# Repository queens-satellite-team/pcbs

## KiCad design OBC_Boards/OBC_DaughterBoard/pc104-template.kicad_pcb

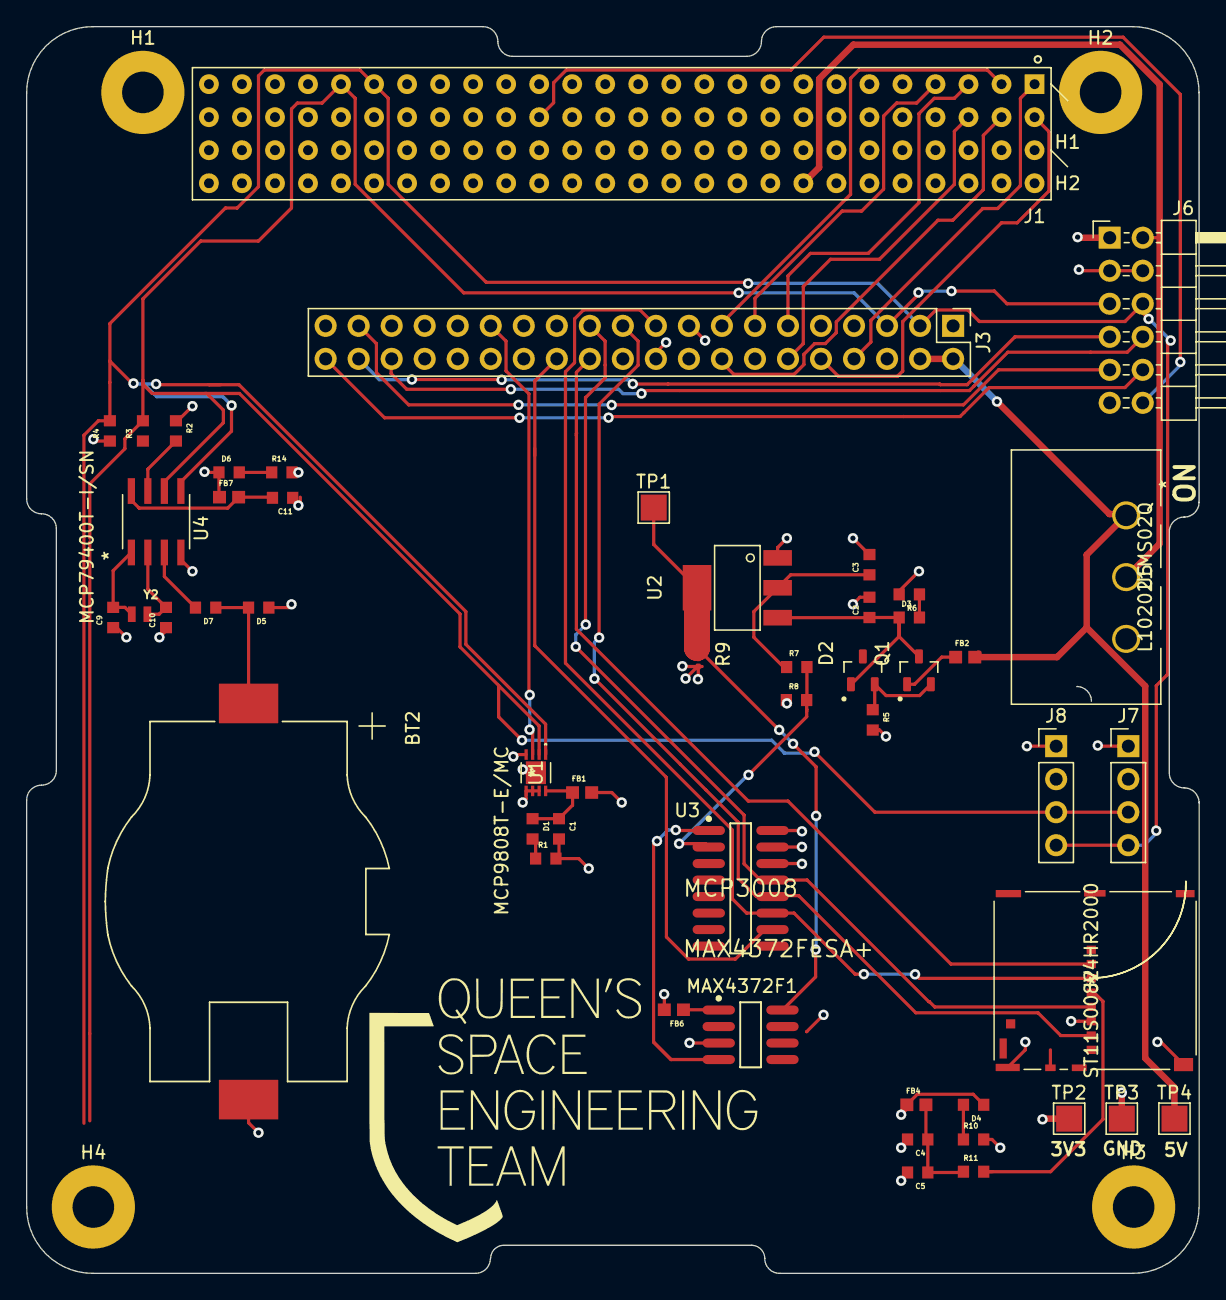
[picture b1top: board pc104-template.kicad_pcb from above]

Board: 4 copper layers, 90.2 x 95.9 mm, 55 parts (0 on the bottom side), 47 nets.

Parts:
BT2: BHSD-2032-SM; BAT_BHSD-2032-SM
C1, C4: 0.1uF; CAPC1608X90N
C2, C5, C11: 10uF; CAPC1608X90N
C3: 22uF; CAPC1608X90N
C9, C10: 18pF; CAPC1608X90N
D1, D3, D4, D6: RED; CAPC1608X90N
D2: D_Zener; SOT91P240X110-3N
D5, D7: DIODE; CAPC1608X90N
FB1, FB2, FB4, FB6, FB7: 100R @ 100 MHz; BEADC1608X75N
H1, H2, H3, H4: MountingHole_Pad; MountingHole_3.2mm_M3_Pad
J1: PC104_Connector; pc104-connector
J2: ST11S008V4HR2000
J3: Raspberry Pi 4 Connector; PinHeader_2x20_P2.54mm_Vertical
J6: Test Connector; PinHeader_2x06_P2.54mm_Horizontal
J7: Temp Sens1 Connector; PinHeader_1x04_P2.54mm_Vertical
J8: Temp Sens2 Connector; PinHeader_1x04_P2.54mm_Vertical
MAX4372F1: MAX4372FESA+; Maxim-MAX4372FESA+-Level_A
Q1: Q_PMOS_DGS; SOT91P240X110-3N
R1, R6, R10, R14: 2.2k; RESC1608X55N
R2, R3, R4, R5, R8: 10k; RESC1608X55N
R7: 20k; RESC1608X55N
R9: 100m; R_0201_0603Metric
R11: 33; RESC1608X55N
TP1, TP3: TestPoint; TestPoint_Pad_2.0x2.0mm
TP2: 3V3; TestPoint_Pad_2.0x2.0mm
TP4: 5V; TestPoint_Pad_2.0x2.0mm
U1: MCP9808T-E/MC; MCP9808T-E&slash_MC
U2: BU33SA5WGWZ-E2-qsat-symb; BU33SA5WGWZ-E2
U3: MCP3008; Microchip-MCP3008-I_SL-Level_A
U4: MCP79400T-I/SN; MCP79400T-I&slash_SN
U5: L102021MS02Q
Y2: CM9V-T1A; XTAL_CM9V-T1A-32.768KHZ-9PF-20PPM-TA-QC

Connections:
3V3_Input: J7.1, J8.1
5VUSB_CHG: J1.32 (H1-32), J6.12
+3.3V: D6.1 (A), FB7.1, R2.1, R3.1, R4.1
+3V3: D4.1 (A), D5.1 (A), FB1.2, FB4.1, FB6.2, J3.1, J3.17, MAX4372F1.6 (RS-), R9.2, TP2.1, U3.15 (Vref), U3.16 (Vdd)
+5V: FB2.2, J3.2, J3.4, TP4.1, U5.1
/Current Monitor/CH1: R7.2, R8.2, U3.2 (CH1)
/Current Monitor/PM_Input: MAX4372F1.8 (RS+), R9.1, TP1.1, U2.4 (Vout)
ADCS_INT: J1.5 (H1-5), J3.11
BAT_INT: J1.7 (H1-7), J3.13
COMM_CTS: J1.3 (H1-3), J3.15
COMM_RTS: J1.4 (H1-4), J3.16
COMM_RXD: J1.2 (H1-2), J3.10
COMM_TXD: J1.1 (H1-1), J3.8
EPS_INT: J1.6 (H1-6), J3.12
GND: BT2.-, C1.2, C2.1, C3.2, C4.2, C5.2, C9.1, C10.1, C11.1, H1.1, H2.1, H3.1, H4.1, J1.61 (H2-9), J1.66 (H1-14), J1.69 (H2-17), J1.73 (H2-21), J1.74 (H1-22), J1.81 (H2-29), J1.82 (H1-30), J1.84 (H1-32), J1.99 (H2-47), J1.100 (H2-48), J2.6 (VSS), J2.11 (GND1), J2.12 (GND2), J2.13 (GND3), J2.14 (GND4), J2.15 (GND5), J2.16 (GND6), J2.17 (GND7), J3.6, J3.9, J3.14, J3.20, J3.25, J3.30, J3.34, J3.39, J6.3, J6.4, J7.2, J8.2, MAX4372F1.3 (GND), R1.2, R5.2, R6.2, R8.1, R10.2, R14.2, TP3.1, U1.4 (GND), U1.5 (A2), U1.6 (A1), U1.7 (A0), U1.9 (EPAD), U2.1 (GND), U3.14 (AGND), U4.4 (VSS)
GPIO5: J3.29, U1.3 (ALERT)
GPIO16: J3.36, J6.8
GPIO20: J3.38, J6.7
GPIO21: J3.40, J6.10
GPIO26: J3.37, J6.9
I2C_SCL1: J1.43 (H1-43), J3.5, J6.5, J7.3, J8.3, R3.2, U1.2 (SCL), U4.6 (SCL)
I2C_SDA1: J1.41 (H1-41), J3.3, J6.6, J7.4, J8.4, R4.2, U1.1 (SDA), U4.5 (SDA)
unnamed: BT2.+, D5.2 (K), D7.1 (A)
unnamed: C1.1, D1.1 (A), FB1.1, U1.8 (VDD)
unnamed: C2.2, D2.1 (K), D3.1 (A), Q1.3 (S), U2.3 (Input)
unnamed: C3.1, R7.1, U2.2 (Output)
unnamed: C4.1, C5.1, FB4.2, R11.1
unnamed: C11.2, FB7.2, U4.8 (VCC)
unnamed: D1.2 (K), R1.1
unnamed: D2.2 (A), Q1.2 (G), R5.1
unnamed: D3.2 (K), R6.1
unnamed: D4.2 (K), R10.1
unnamed: D6.2 (K), R14.1
unnamed: FB2.1, Q1.1 (D)
unnamed: FB6.1, MAX4372F1.1 (VCC)
unnamed: J2.4 (VDD), R11.2
unnamed: MAX4372F1.4 (OUT), U3.1 (CH0)
RTC_MFP: R2.2, U4.7 (MFP)
SPI1_CE0_N: J2.2 (CS/DAT3), J3.24
SPI1_CE1_N: J3.26, U3.10 (~CS/SHDN)
SPI1_CLK: J2.5 (CLK), J3.23, U3.13 (CLK)
SPI1_MISO: J2.7 (DAT0/DO), J3.21, U3.12 (Dout)
SPI1_MOSI: J2.3 (CMD/DI), J3.19, U3.11 (Din)
SW7_5V_Input: J1.68 (H1-16), J6.2, U5.2
VCC_BAT: D7.2 (K), U4.3 (VBAT)
XCO1: C9.2, U4.1 (X1), Y2.1
XCO2: C10.2, U4.2 (X2), Y2.2

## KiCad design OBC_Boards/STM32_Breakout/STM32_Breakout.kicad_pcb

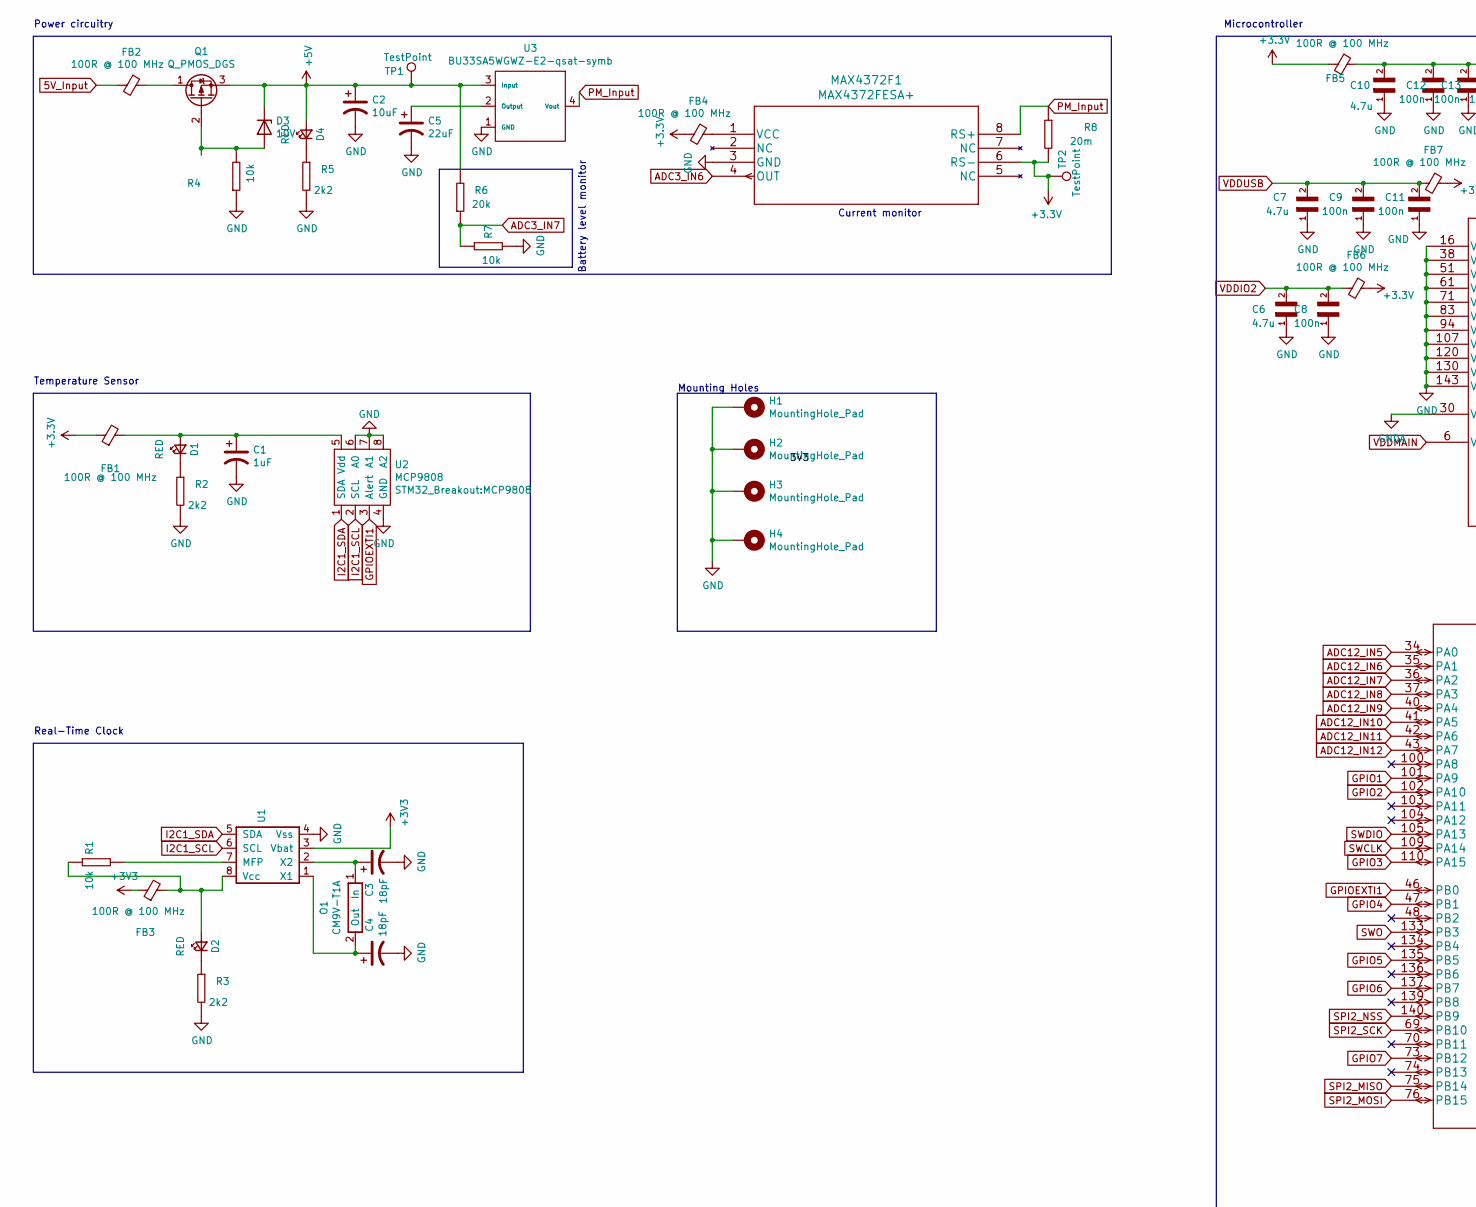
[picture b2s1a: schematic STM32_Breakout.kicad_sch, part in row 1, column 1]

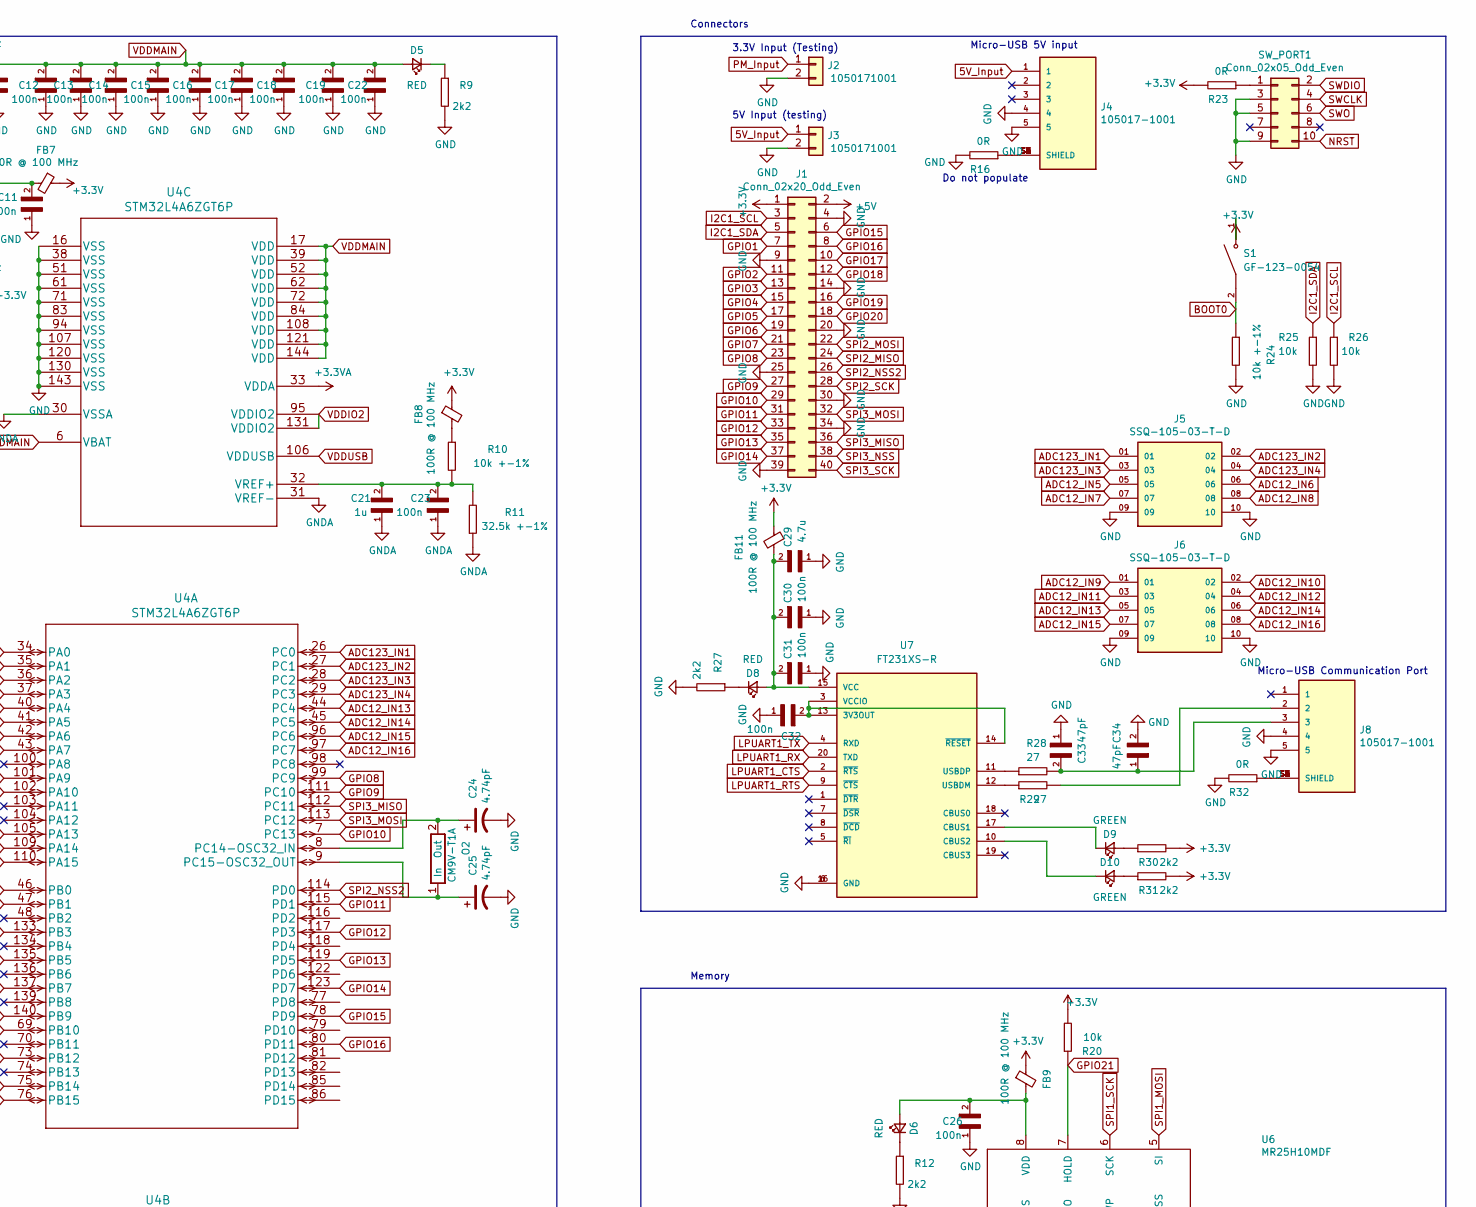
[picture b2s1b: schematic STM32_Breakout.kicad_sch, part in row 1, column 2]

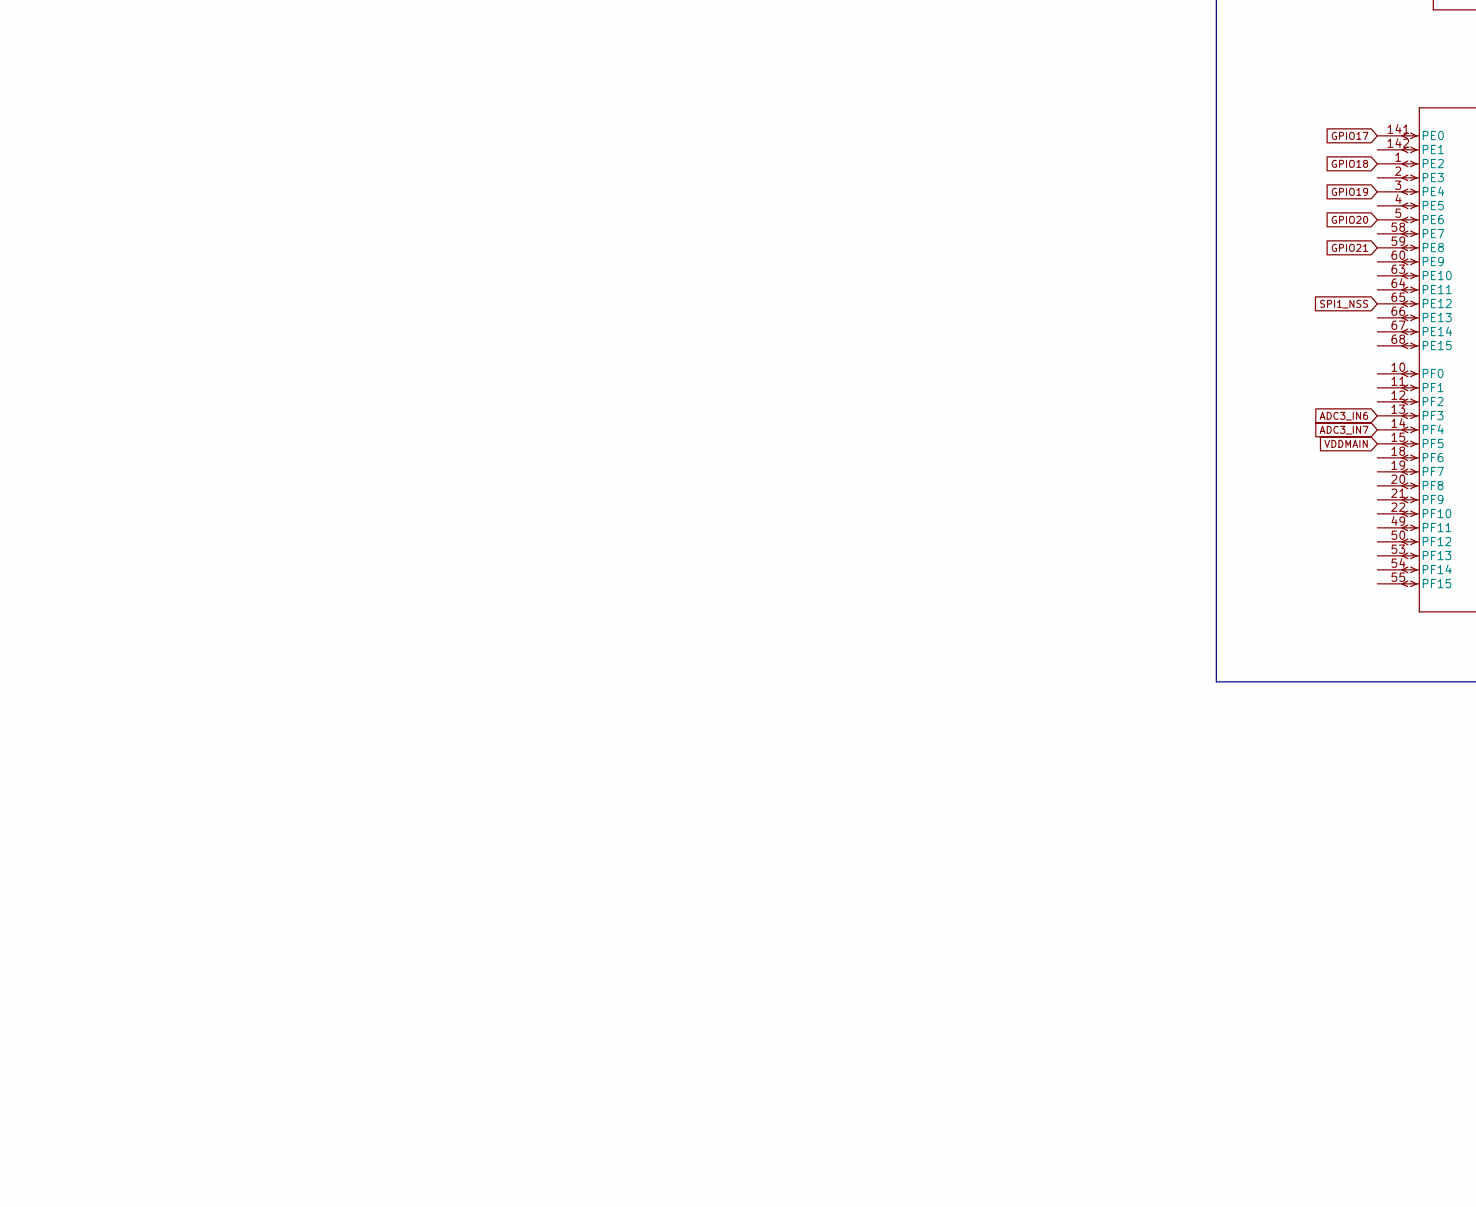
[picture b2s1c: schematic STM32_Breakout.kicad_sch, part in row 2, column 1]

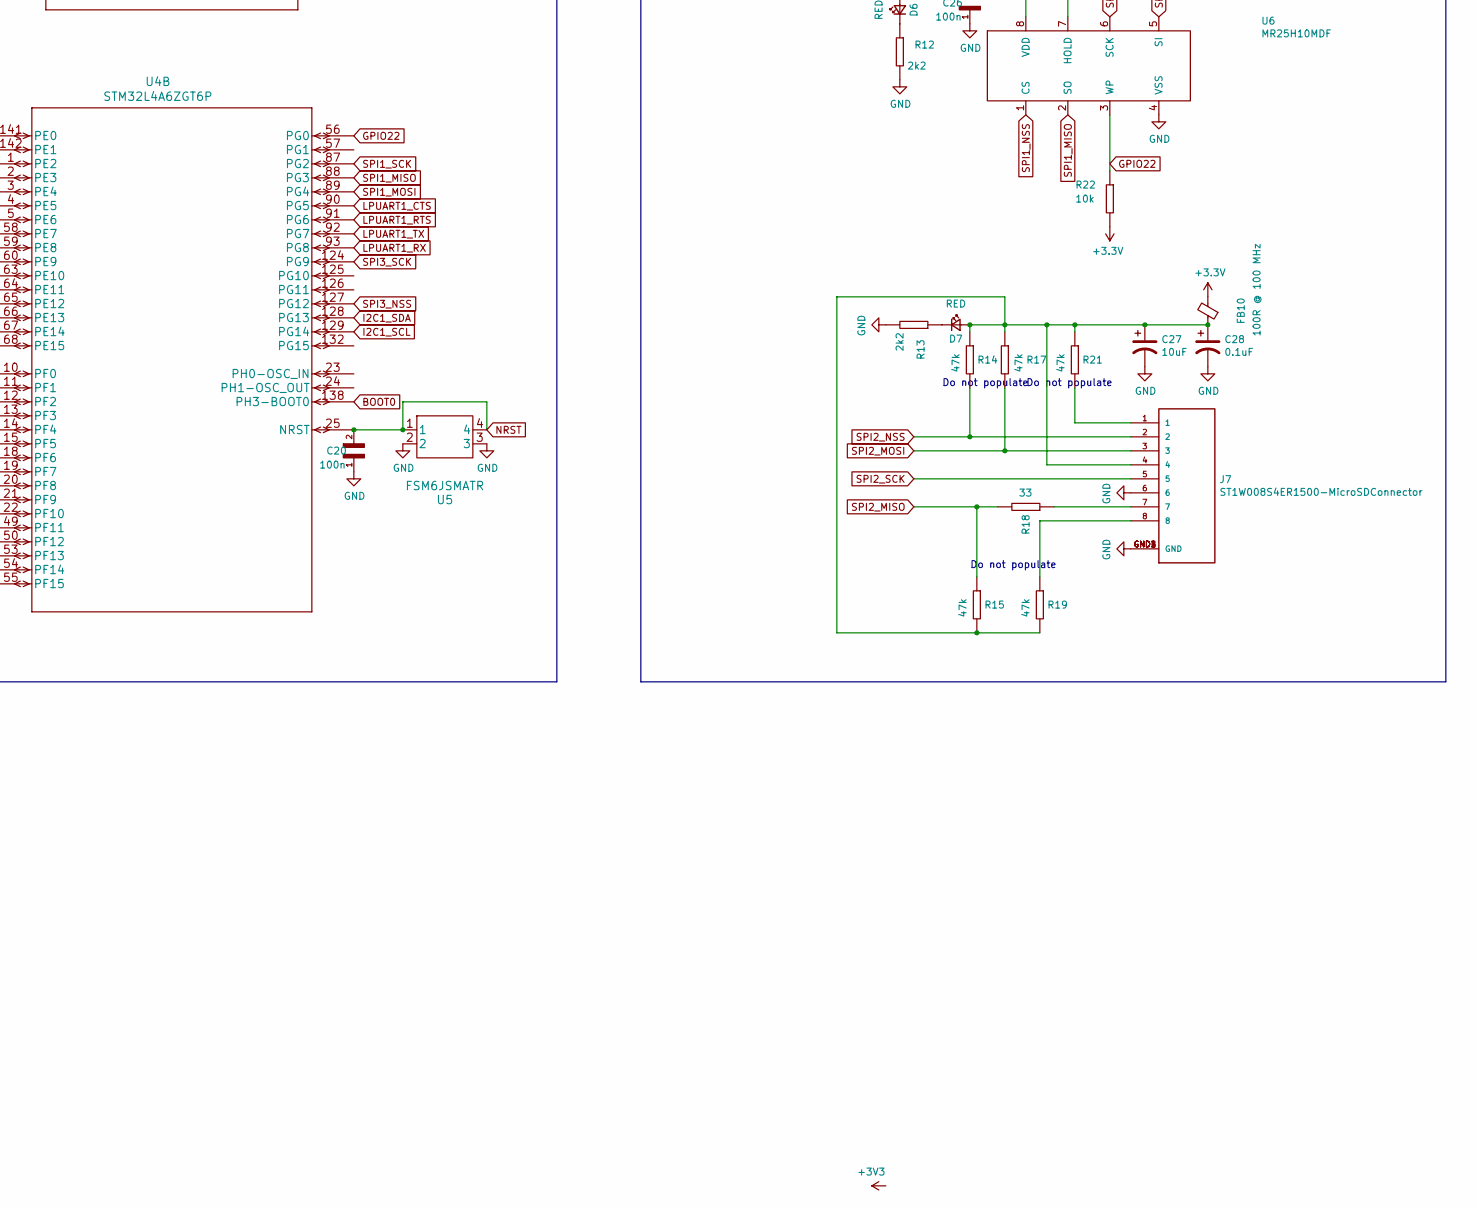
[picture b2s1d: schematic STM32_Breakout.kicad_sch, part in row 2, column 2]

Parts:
C1: 1uF; CAPC1608X90
C2, C27: 10uF; CAPC1608X90
C3, C4: 18pF; CAPC1608X90
C5: 22uF; CAPC1608X90
C6, C7, C10, C29: 4.7u; CAPC1608X90
C8, C9, C11, C12, C13, C14, C15, C16, C17, C18, C19, C20, C22, C23, C26, C30, C31, C32: 100n; CAPC1608X90
C21: 1u; CAPC1608X90
C24, C25: 4.74pF; CAPC1608X90
C28: 0.1uF; CAPC1608X90
C33, C34: 47pF; CAPC1608X90
D1, D2, D4, D5, D6, D7, D8: RED; LED_0603_1608Metric_Pad1.05x0.95mm_HandSolder
D3: 10V; SOT91P240X110-3N
D9, D10: GREEN; LED_0603_1608Metric_Pad1.05x0.95mm_HandSolder
FB1, FB2, FB3, FB4, FB5, FB6, FB7, FB8, FB9, FB10, FB11: 100R @ 100 MHz; INDUC1607X60N
H1, H2, H3, H4: MountingHole_Pad; MountingHole_4.3mm_M4_Pad_Via
J1: Conn_02x20_Odd_Even; PinHeader_2x20_P2.54mm_Vertical
J2, J3: 1050171001; PinHeader_1x02_P2.54mm_Vertical
J4, J8: 105017-1001; MOLEX_105017-1001; PARTREV F
J5, J6: SSQ-105-03-T-D; SAMTEC_SSQ-105-03-T-D; PARTREV R
J7: ST1W008S4ER1500-MicroSDConnector; JAE_ST1W008S4ER1500; PARTREV 2
MAX4372F1: MAX4372FESA+; SOIC127P600X175-8N
O1, O2: CM9V-T1A
Q1: Q_PMOS_DGS; SOT91P240X110-3N
R1, R4, R7, R20, R22, R25, R26: 10k; RESC1607X60N
R2, R3, R5, R9, R12, R13, R27, R30, R31: 2k2; RESC1607X60N
R6: 20k; RESC1607X60N
R8: 20m; RESC1607X60N
R10, R24: 10k +-1%; RESC1607X60N
R11: 32.5k +-1%; RESC1607X60N
R14, R15, R17, R19, R21: 47k; RESC1607X60N
R16, R23, R32: 0R; RESC1607X60N
R18: 33; RESC1607X60N
R28, R29: 27; RESC1607X60N
S1: GF-123-0054; SW_GF-123-0054; PARTREV May 20, 2003
SW_PORT1: Conn_02x05_Odd_Even; PinHeader_2x05_P1.27mm_Vertical_SMD
TP1, TP2: TestPoint; TestPoint_Pad_D2.0mm
U1: MCP7940NT-I_MS; MCP7940NT-I-MS
U2: MCP9808
U3: BU33SA5WGWZ-E2-qsat-symb; BU33SA5WGWZ-E2
U4: STM32L4A6ZGT6P; LQFP144-20x20mm
U5: FSM6JSMATR
U6: MR25H10MDF; SON65P300X300X95-8N
U7: FT231XS-R; SOP63P599X175-20N; PARTREV 1.2

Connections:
5V_Input: FB2.2, J3.1, J4.1
+3.3VA: U4.33 (VDDA)
+5V: C2.1, D3.1 (K), D4.2 (A), J1.2, Q1.3 (S), R6.2, TP1.1, U3.3 (Input)
ADC3_IN6: MAX4372F1.4 (OUT), U4.13 (PF3)
ADC3_IN7: R6.1, R7.1, U4.14 (PF4)
ADC12_IN5: J5.05, U4.34 (PA0)
ADC12_IN6: J5.06, U4.35 (PA1)
ADC12_IN7: J5.07, U4.36 (PA2)
ADC12_IN8: J5.08, U4.37 (PA3)
ADC12_IN9: J6.01, U4.40 (PA4)
ADC12_IN10: J6.02, U4.41 (PA5)
ADC12_IN11: J6.03, U4.42 (PA6)
ADC12_IN12: J6.04, U4.43 (PA7)
ADC12_IN13: J6.05, U4.44 (PC4)
ADC12_IN14: J6.06, U4.45 (PC5)
ADC12_IN15: J6.07, U4.96 (PC6)
ADC12_IN16: J6.08, U4.97 (PC7)
ADC123_IN1: J5.01, U4.26 (PC0)
ADC123_IN2: J5.02, U4.27 (PC1)
ADC123_IN3: J5.03, U4.28 (PC2)
ADC123_IN4: J5.04, U4.29 (PC3)
BOOT0: R24.1, S1.2, U4.138 (PH3-BOOT0)
GND: C1.2, C2.2, C3.2, C4.2, C5.2, C6.1, C7.1, C8.1, C9.1, C10.1, C11.1, C12.1, C13.1, C14.1, C15.1, C16.1, C17.1, C18.1, C19.1, C20.1, C22.1, C24.2, C25.2, C26.1, C27.2, C28.2, C29.1, C30.1, C31.1, C32.1, C33.1, C34.2, H1.1, H2.1, H3.1, H4.1, J1.4, J1.9, J1.14, J1.20, J1.25, J1.30, J1.34, J1.39, J2.2, J3.2, J4.4, J4.5, J5.09, J5.10, J6.09, J6.10, J7.6, J7.GND1 (GND), J7.GND2 (GND), J7.GND3 (GND), J7.GND4 (GND), J8.4, J8.5, MAX4372F1.3 (GND), R2.2, R3.2, R4.1, R5.2, R7.2, R9.2, R12.2, R13.2, R16.2, R24.2, R25.2, R26.2, R27.2, R32.2, SW_PORT1.3, SW_PORT1.5, SW_PORT1.9, U1.4 (Vss), U2.4 (GND), U2.6 (A0), U2.7 (A1), U2.8 (A2), U3.1 (GND), U4.16 (VSS), U4.38 (VSS), U4.51 (VSS), U4.61 (VSS), U4.71 (VSS), U4.83 (VSS), U4.94 (VSS), U4.107 (VSS), U4.120 (VSS), U4.130 (VSS), U4.143 (VSS), U5.2, U5.3, U6.4 (VSS), U7.6 (GND), U7.16 (GND)
GNDA: C21.1, C23.1, R11.1, U4.30 (VSSA), U4.31 (VREF-)
GPIO1: J1.7, U4.101 (PA9)
GPIO2: J1.11, U4.102 (PA10)
GPIO3: J1.13, U4.110 (PA15)
GPIO4: J1.15, U4.47 (PB1)
GPIO5: J1.17, U4.135 (PB5)
GPIO6: J1.19, U4.137 (PB7)
GPIO7: J1.21, U4.73 (PB12)
GPIO8: J1.23, U4.99 (PC9)
GPIO9: J1.27, U4.111 (PC10)
GPIO10: J1.29, U4.7 (PC13)
GPIO11: J1.31, U4.115 (PD1)
GPIO12: J1.33, U4.117 (PD3)
GPIO13: J1.35, U4.119 (PD5)
GPIO14: J1.37, U4.123 (PD7)
GPIO15: J1.6, U4.78 (PD9)
GPIO16: J1.8, U4.80 (PD11)
GPIO17: J1.10, U4.141 (PE0)
GPIO18: J1.12, U4.1 (PE2)
GPIO19: J1.16, U4.3 (PE4)
GPIO20: J1.18, U4.5 (PE6)
GPIO21: R20.1, U4.59 (PE8), U6.7 (HOLD)
GPIO22: R22.1, U4.56 (PG0), U6.3 (WP)
GPIOEXTI1: U2.3 (Alert), U4.46 (PB0)
I2C1_SCL: J1.3, R26.1, U1.6 (SCL), U2.2 (SCL), U4.129 (PG14)
I2C1_SDA: J1.5, R25.1, U1.5 (SDA), U2.1 (SDA), U4.128 (PG13)
LPUART1_CTS: U4.90 (PG5), U7.2 (~RTS)
LPUART1_RTS: U4.91 (PG6), U7.9 (~CTS)
LPUART1_RX: U4.93 (PG8), U7.20 (TXD)
LPUART1_TX: U4.92 (PG7), U7.4 (RXD)
NRST: C20.2, SW_PORT1.10, U4.25 (NRST), U5.1, U5.4
unnamed: C1.1, D1.2 (A), FB1.2, U2.5 (Vdd)
unnamed: C3.1, O1.1 (In), U1.2 (X2)
unnamed: C4.1, O1.2 (Out), U1.1 (X1)
unnamed: C5.1, U3.2 (Output)
unnamed: C21.2, C23.2, R10.2, R11.2, U4.32 (VREF+)
unnamed: C24.1, O2.2 (Out), U4.8 (PC14-OSC32_IN)
unnamed: C25.1, O2.1 (In), U4.9 (PC15-OSC32_OUT)
unnamed: C26.2, D6.2 (A), FB9.2, U6.8 (VDD)
unnamed: C29.2, C30.2, C31.2, D8.2 (A), FB11.2, U7.15 (VCC)
unnamed: C32.2, U7.3 (VCCIO), U7.13 (3V3OUT), U7.14 (~RESET)
unnamed: C33.2, C34.1, J8.3, R28.2
unnamed: D1.1 (K), R2.1
unnamed: D2.1 (K), R3.1
unnamed: D2.2 (A), FB3.2, R1.1, U1.8 (Vcc)
unnamed: D3.2 (A), Q1.2 (G), R4.2
unnamed: D4.1 (K), R5.1
unnamed: D5.1 (K), R9.1
unnamed: D6.1 (K), R12.1
unnamed: D7.1 (K), R13.1
unnamed: D8.1 (K), R27.1
unnamed: D9.1 (K), U7.17 (CBUS1)
unnamed: D9.2 (A), R30.1
unnamed: D10.1 (K), U7.10 (CBUS2)
unnamed: D10.2 (A), R31.1
unnamed: FB2.1, Q1.1 (D)
unnamed: FB4.1, MAX4372F1.1 (VCC)
unnamed: FB8.2, R10.1
unnamed: J4.S1 (SHIELD), J4.S2 (SHIELD), J4.S3 (SHIELD), J4.S4 (SHIELD), J4.S5 (SHIELD), J4.S6 (SHIELD), R16.1
unnamed: J7.1, R21.2
unnamed: J7.7, R18.1
unnamed: J7.8, R19.1
unnamed: J8.2, R29.2
unnamed: J8.S1 (SHIELD), J8.S2 (SHIELD), J8.S3 (SHIELD), J8.S4 (SHIELD), J8.S5 (SHIELD), J8.S6 (SHIELD), R32.1
unnamed: R1.2, U1.7 (MFP)
unnamed: C27.1, C28.1, D7.2 (A), FB10.1, J7.4, R14.1, R15.2, R17.1, R19.2, R21.1
unnamed: R28.1, U7.11 (USBDP)
unnamed: R29.1, U7.12 (USBDM)
unnamed: R23.1, SW_PORT1.1
PM_Input: J2.1, MAX4372F1.8 (RS+), R8.1, U3.4 (Vout)
SPI1_MISO: U4.88 (PG3), U6.2 (SO)
SPI1_MOSI: U4.89 (PG4), U6.5 (SI)
SPI1_NSS: U4.65 (PE12), U6.1 (CS)
SPI1_SCK: U4.87 (PG2), U6.6 (SCK)
SPI2_MISO: J1.24, R15.1, R18.2, U4.75 (PB14)
SPI2_MOSI: J1.22, J7.3, R17.2, U4.76 (PB15)
SPI2_NSS: J7.2, R14.2, U4.140 (PB9)
SPI2_NSS2: J1.26, U4.114 (PD0)
SPI2_SCK: J1.28, J7.5, U4.69 (PB10)
SPI3_MISO: J1.36, U4.112 (PC11)
SPI3_MOSI: J1.32, U4.113 (PC12)
SPI3_NSS: J1.38, U4.127 (PG12)
SPI3_SCK: J1.40, U4.124 (PG9)
SWCLK: SW_PORT1.4, U4.109 (PA14)
SWDIO: SW_PORT1.2, U4.105 (PA13)
SWO: SW_PORT1.6, U4.133 (PB3)
VDDIO2: C6.2, C8.2, FB6.2, U4.95 (VDDIO2), U4.131 (VDDIO2)
VDDMAIN: C10.2, C12.2, C13.2, C14.2, C15.2, C16.2, C17.2, C18.2, C19.2, C22.2, D5.2 (A), FB5.1, U4.6 (VBAT), U4.15 (PF5), U4.17 (VDD), U4.39 (VDD), U4.52 (VDD), U4.62 (VDD), U4.72 (VDD), U4.84 (VDD), U4.108 (VDD), U4.121 (VDD), U4.144 (VDD)
VDDUSB: C7.2, C9.2, C11.2, FB7.2, U4.106 (VDDUSB)

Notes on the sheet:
Current monitor
Power circuitry
Mounting Holes
Memory
Do not populate
3.3V Input (Testing)
5V Input (testing)
Connectors
Real-Time Clock
Temperature Sensor
Micro-USB Communication Port
Battery level monitor
Microcontroller
Micro-USB 5V input

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
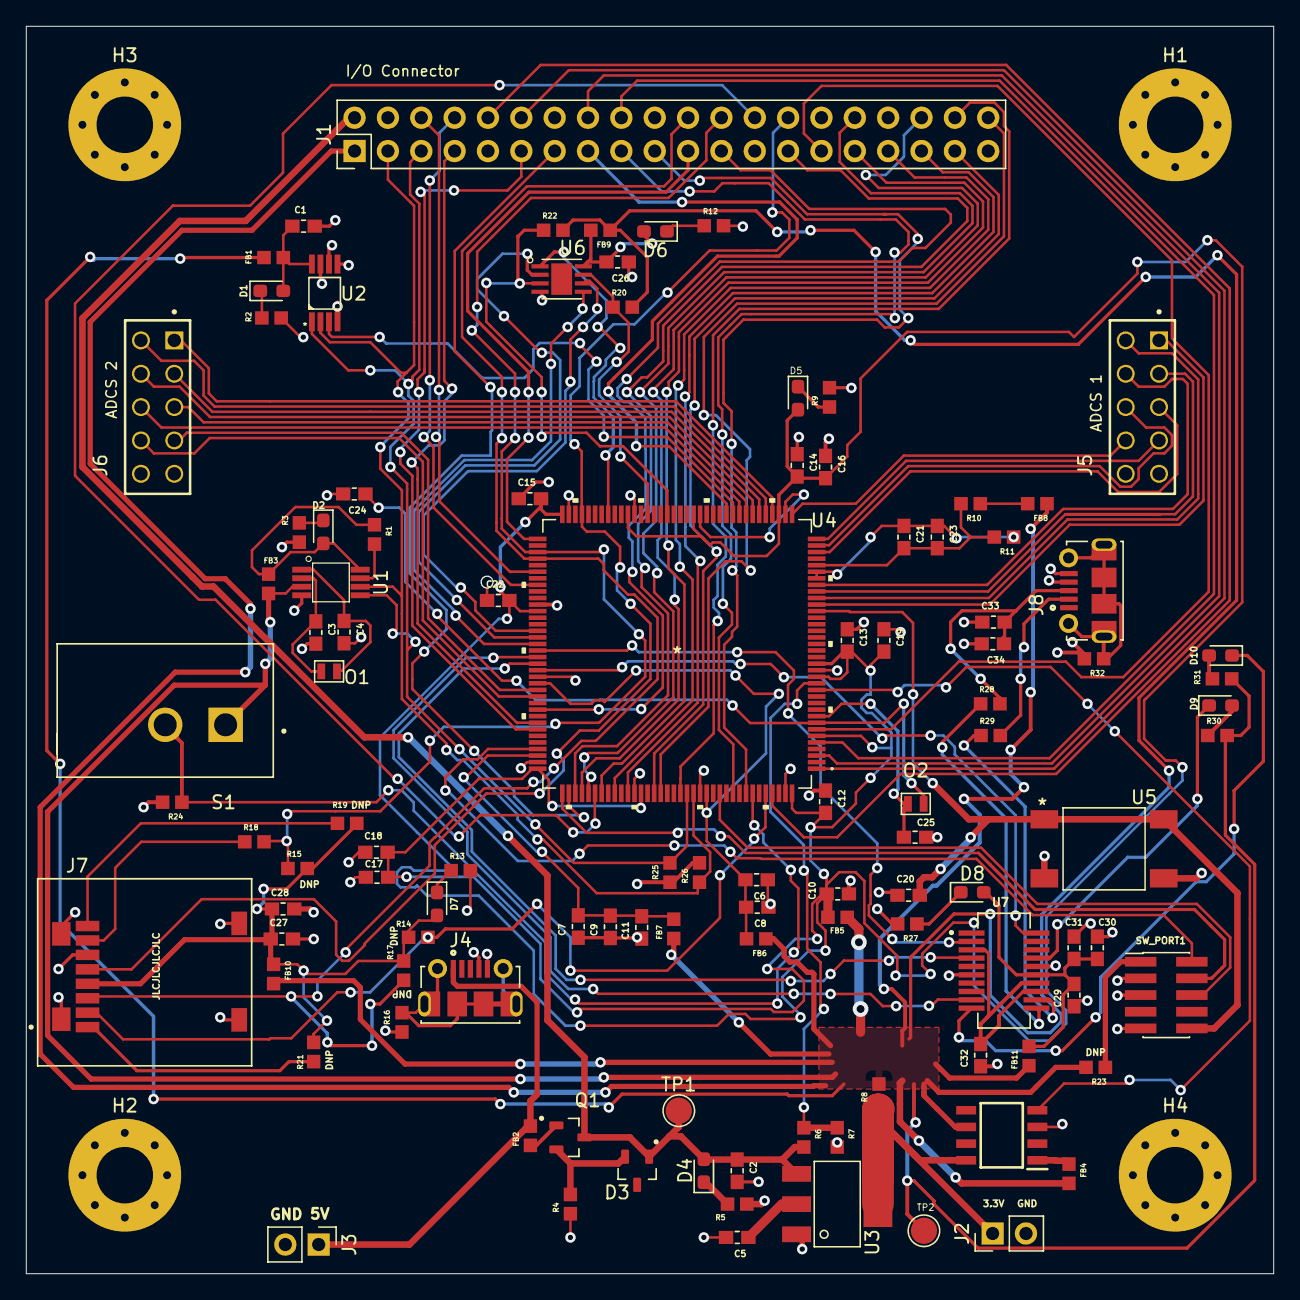
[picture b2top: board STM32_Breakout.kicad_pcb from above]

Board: 4 copper layers, 95.0 x 95.0 mm, 114 parts (0 on the bottom side), 112 nets.

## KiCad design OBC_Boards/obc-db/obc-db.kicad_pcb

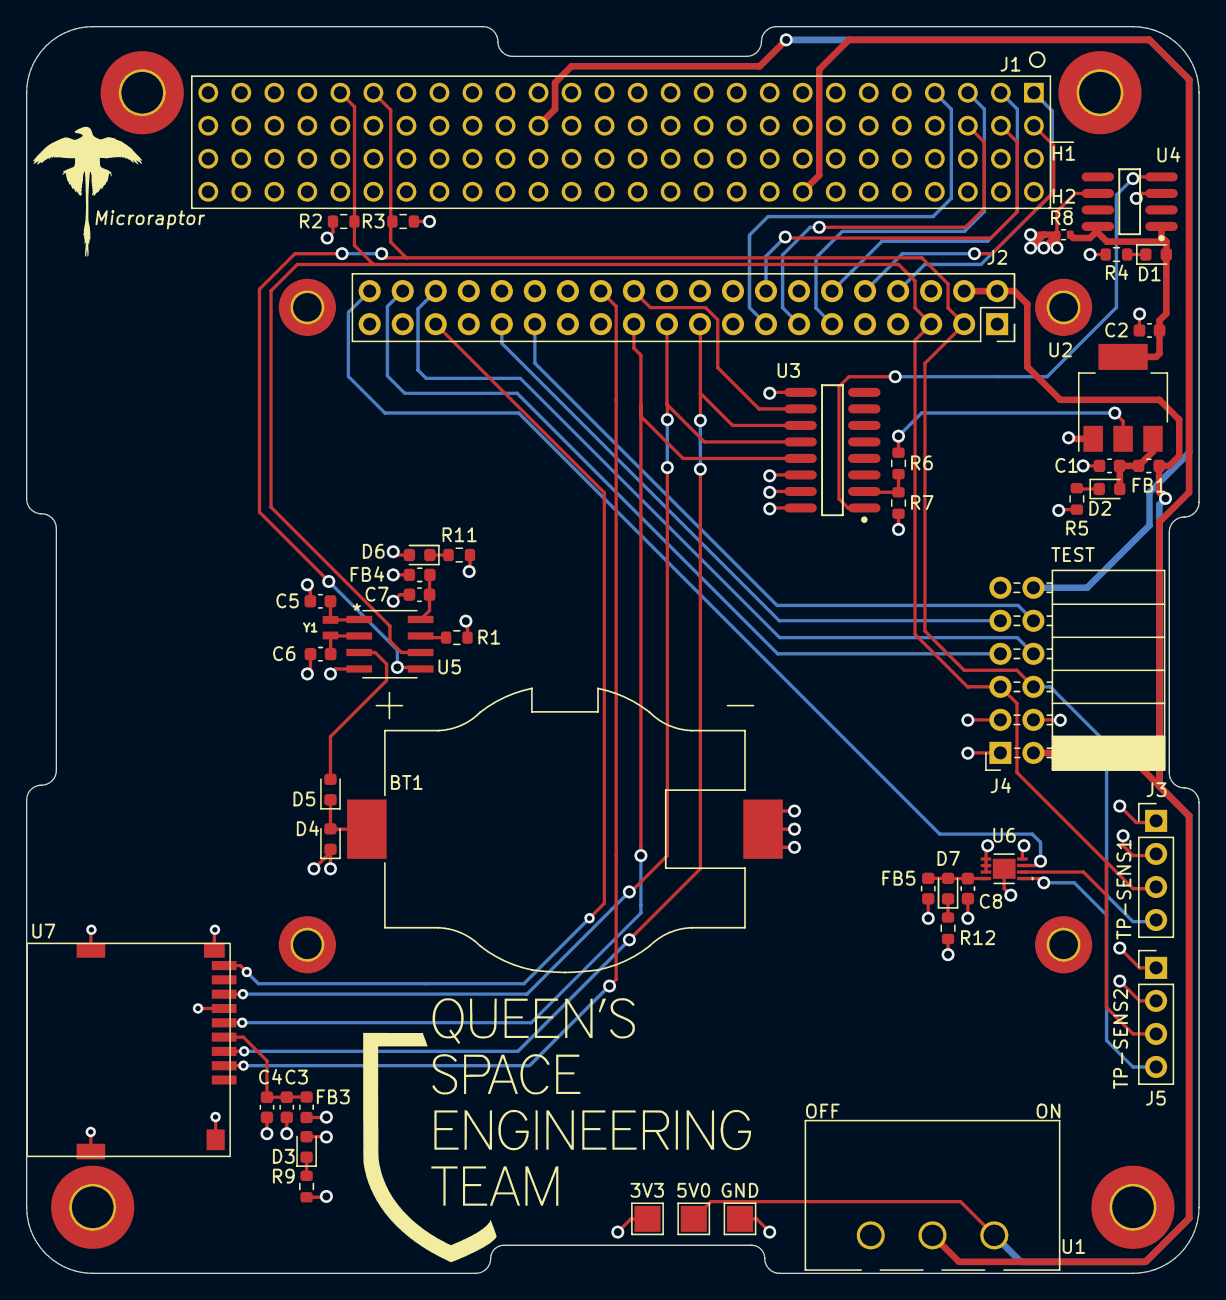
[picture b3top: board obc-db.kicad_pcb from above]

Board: 4 copper layers, 90.2 x 95.9 mm, 55 parts (0 on the bottom side), 43 nets.

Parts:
BT1: BHSD-2032-SM; BAT_BHSD-2032-SM
C1, C2: 22uF; C_0603_1608Metric
C3, C7: 10uF; C_0603_1608Metric
C4, C8: 0.1uF; C_0603_1608Metric
C5, C6: 18pF; C_0603_1608Metric
D1, D2, D3, D6, D7: LED; LED_0603_1608Metric
D4, D5: DIODE; D_0603_1608Metric
FB1, FB3, FB4, FB5: 100R @ 100 MHz; L_0603_1608Metric
H1, H2, H3, H4: MountingHole_Pad; MountingHole_3.2mm_M3_Pad_TopBottom
H5, H6, H7, H8: MountingHole_Pad; MountingHole_2.2mm_M2_Pad_TopBottom
J1: PC104_Connector; pc104-connector
J2: Raspberry Pi 4 Connector; PinSocket_2x20_P2.54mm_Vertical
J3: Temp Sens1 Connector; PinHeader_1x04_P2.54mm_Vertical
J4: Test Connector; PinSocket_2x06_P2.54mm_Horizontal
J5: Temp Sens2 Connector; PinHeader_1x04_P2.54mm_Vertical
R1, R2, R3, R7: 10k; R_0603_1608Metric
R4, R5, R9, R11, R12: 2.2k; R_0603_1608Metric
R6: 20k; R_0603_1608Metric
R8: 100m; R_0402_1005Metric
TP1: 3V3; TestPoint_Pad_2.0x2.0mm
TP2: 5V0; TestPoint_Pad_2.0x2.0mm
TP3: GND; TestPoint_Pad_2.0x2.0mm
U1: L102021MS02Q
U2: AZ1117IH-3.3TRG1; SOT-223-3_TabPin2
U3: MCP3008-I/SL; Microchip-MCP3008-I_SL-Level_A
U4: MAX4372FESA+; Maxim-MAX4372FESA+-Level_A
U5: MCP79400T-I/SN; MCP79400T-I&slash_SN
U6: MCP9808T-E/MC; MCP9808T-E&slash_MC
U7: MR01A-01211
Y1: CM9V-T1A; XTAL_CM9V-T1A-32.768KHZ-9PF-20PPM-TA-QC

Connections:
5VUSB_CHG: J1.32 (H1-32), J4.12
+3V3: D3.2 (A), D4.1 (A), D6.2 (A), FB3.1, FB4.1, FB5.1, J3.1, J4.1, J5.1, R1.1, R2.1, R3.1, R8.2, TP1.1, U3.15 (Vref), U3.16 (Vdd), U4.6 (RS-)
+5V: FB1.2, J2.2, J2.4, TP2.1, U1.1
/current-monitor/CH1: R6.2, R7.1, U3.2 (CH1)
/current-monitor/PM_Input: C2.1, D1.2 (A), R6.1, R8.1, U2.2 (VO), U4.1 (VCC), U4.8 (RS+)
ADCS_INT: J1.5 (H1-5), J2.11
BAT_INT: J1.7 (H1-7), J2.15
COMM_CTS: J1.3 (H1-3), J2.12
COMM_RTS: J1.4 (H1-4), J2.16
COMM_RXD: J1.2 (H1-2), J2.10
COMM_TXD: J1.1 (H1-1), J2.8
EPS_INT: J1.6 (H1-6), J2.13
GND: BT1.-, C1.1, C2.2, C3.2, C4.2, C5.1, C6.1, C7.1, C8.2, J1.61 (H2-9), J1.66 (H2-14), J1.69 (H2-17), J1.73 (H2-21), J1.74 (H2-22), J1.81 (H2-29), J1.82 (H2-30), J1.84 (H2-32), J1.99 (H2-47), J1.100 (H2-48), J2.6, J2.9, J2.14, J2.20, J2.25, J2.30, J2.34, J2.39, J3.2, J4.3, J4.4, J5.2, R4.2, R5.2, R7.2, R9.2, R11.2, R12.2, TP3.1, U2.1 (GND), U3.9 (DGND), U3.14 (AGND), U4.3 (GND), U5.4 (VSS), U6.4 (GND), U6.5 (A2), U6.6 (A1), U6.7 (A0), U6.9 (EPAD), U7.6 (VSS), U7.10 (GND), U7.11 (GND), U7.12 (GND), U7.13 (GND)
GPIO5: J2.29, J4.10
GPIO6: J2.31, J4.9
GPIO16: J2.36, J4.8
GPIO19: J2.35, U7.9 (CARD_DET)
GPIO20: J2.38, J4.7
GPIO21: J2.40, U6.3 (ALERT)
I2C_SCL1: J1.43 (H1-43), J2.5, J3.3, J4.5, J5.3, R2.2, U5.6 (SCL), U6.2 (SCL)
I2C_SDA1: J1.41 (H1-41), J2.3, J3.4, J4.6, J5.4, R3.2, U5.5 (SDA), U6.1 (SDA)
unnamed: BT1.+, D4.2 (K), D5.1 (A)
unnamed: C1.2, D2.2 (A), FB1.1, U2.3 (VI)
unnamed: C3.1, C4.1, FB3.2, U7.4 (VDD)
unnamed: C7.2, FB4.2, U5.8 (VCC)
unnamed: C8.1, D7.2 (A), FB5.2, U6.8 (VDD)
unnamed: D1.1 (K), R4.1
unnamed: D2.1 (K), R5.1
unnamed: D3.1 (K), R9.1
unnamed: D6.1 (K), R11.1
unnamed: D7.1 (K), R12.1
unnamed: U3.1 (CH0), U4.4 (OUT)
RTC_MFP: R1.2, U5.7 (MFP)
SPI1_CE0_N: J2.24, U3.10 (~CS/SHDN)
SPI1_CE1_N: J2.26, U7.2 (CD/DAT3)
SPI1_CLK: J2.23, U3.13 (CLK), U7.5 (CLK)
SPI1_MISO: J2.21, U3.12 (Dout), U7.7 (DAT0)
SPI1_MOSI: J2.19, U3.11 (Din), U7.3 (CMD)
SW7_5V_Input: J1.68 (H2-16), J4.2, U1.2
VCC_BAT: D5.2 (K), U5.3 (VBAT)
VCC_RPI_3V3: J2.1, J2.17
XCO1: C5.2, U5.1 (X1), Y1.1
XCO2: C6.2, U5.2 (X2), Y1.2

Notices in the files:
parts and their libraries:
Copyright 2021 Accelerated Designs. All rights reserved.
